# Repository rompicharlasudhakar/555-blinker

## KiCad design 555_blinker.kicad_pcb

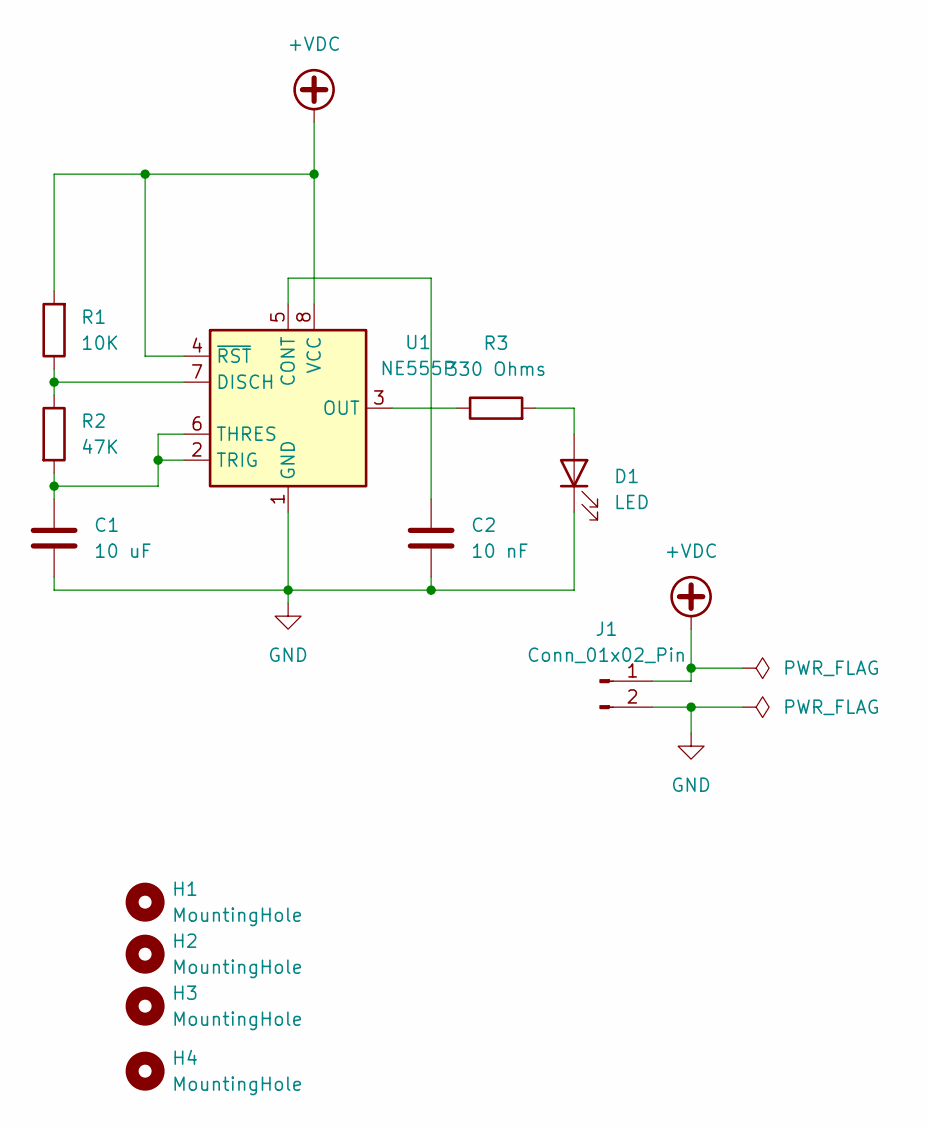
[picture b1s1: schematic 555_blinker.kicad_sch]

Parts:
C1: 10 uF; CP_Radial_D5.0mm_P2.50mm
C2: 10 nF; C_Disc_D5.0mm_W2.5mm_P5.00mm
D1: LED; LED_D5.0mm
H1, H2, H3, H4: MountingHole; MountingHole_3.2mm_M3
J1: Conn_01x02_Pin; PinHeader_1x02_P2.54mm_Vertical
R1: 10K; R_Axial_DIN0204_L3.6mm_D1.6mm_P7.62mm_Horizontal
R2: 47K; R_Axial_DIN0204_L3.6mm_D1.6mm_P7.62mm_Horizontal
R3: 330 Ohms; R_Axial_DIN0204_L3.6mm_D1.6mm_P7.62mm_Horizontal
U1: NE555P; DIP-8_W7.62mm

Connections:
+VDC: J1.1, R1.2, U1.4 (~RST), U1.8 (VCC)
GND: C1.2, C2.2, D1.1 (K), J1.2, U1.1 (GND)
unnamed: D1.2 (A), R3.2
unnamed: C2.1, U1.5 (CONT)
unnamed: R1.1, R2.1, U1.7 (DISCH)
unnamed: R3.1, U1.3 (OUT)
unnamed: C1.1, R2.2, U1.2 (TRIG), U1.6 (THRES)

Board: 2 copper layers, 12 parts (0 on the bottom side), 7 nets, no tracks yet.

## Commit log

2026-06-05 Initial commit: 555 timer LED blinker
